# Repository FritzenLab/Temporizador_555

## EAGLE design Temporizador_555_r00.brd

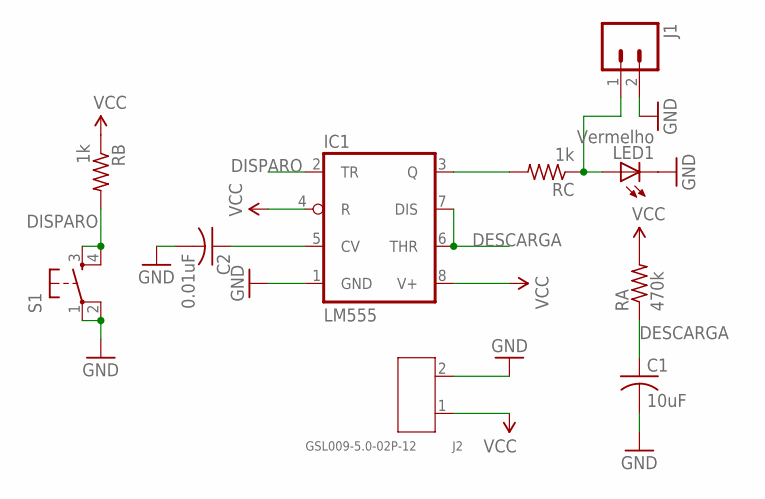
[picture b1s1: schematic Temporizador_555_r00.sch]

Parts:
C1: 10uF; C050-024X044
C2: 0.01uF; C050-024X044
IC1: LM555; DIL08-ROUND
J1: M02PTH; 1X02
J2: GSL009-5.0-02P-12; H2-5.0-10.5X8.0MM
LED1: Vermelho; LED5MM
RA: 470k; 0207/10
RB: 1k; 0207/10
RC: 1k; 0207/10
S1: TACTILE-SWITCH-PTH; TAC-SWITCH-PTH

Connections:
DESCARGA: C1.1, IC1.6 (THR), IC1.7 (DIS), RA.1
DISPARO: IC1.2 (TR), RB.2, S1.3, S1.4
GND: C1.2, C2.2, IC1.1 (GND), J1.2, J2.2, LED1.K (C), S1.1, S1.2
unnamed: C2.1, IC1.5 (CV)
unnamed: J1.1, LED1.A, RC.1
unnamed: IC1.3 (Q), RC.2
VCC: IC1.4 (R), IC1.8 (V+), J2.1, RA.2, RB.1

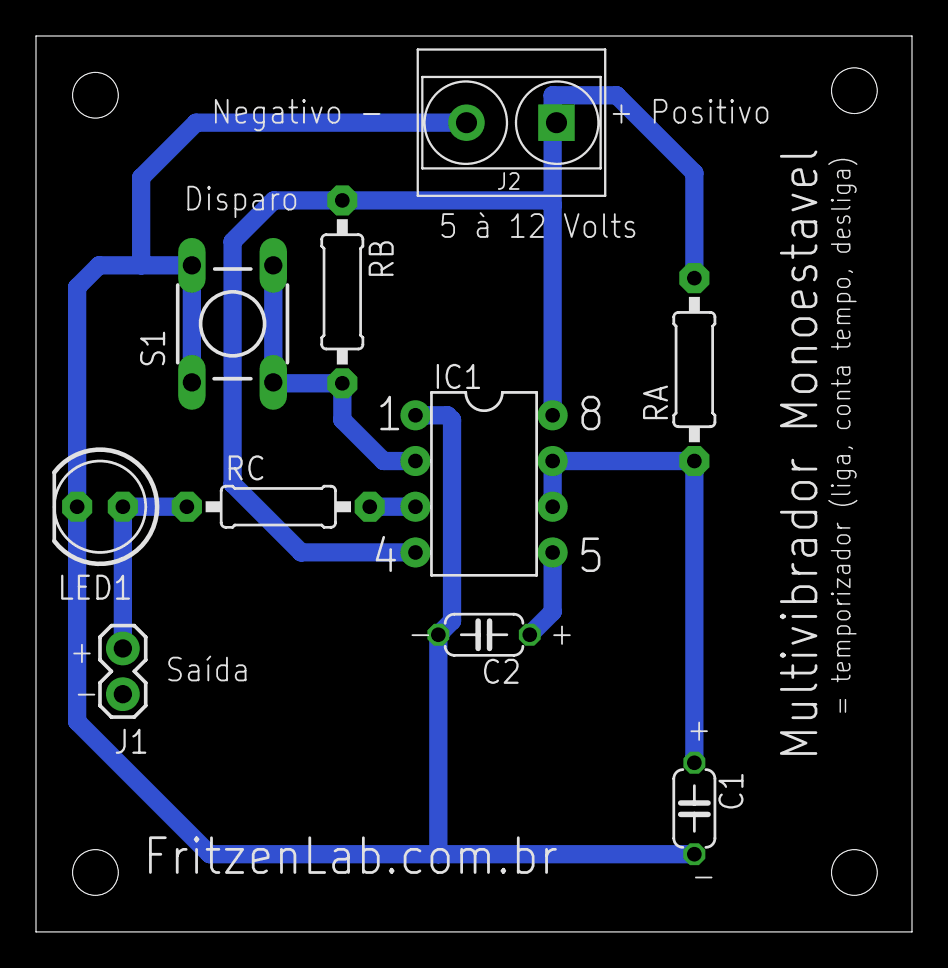
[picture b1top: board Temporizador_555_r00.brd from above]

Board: 2 copper layers, 48.7 x 49.8 mm, 10 parts (0 on the bottom side), 7 nets.

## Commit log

2016-03-02 Lançamento inicial de arquivos
    Upload inicial de diagrama esquematico e placa (layout) do temporizador
    educacional baseado no CI 555, em formato Eagle CAD
2016-04-01 Primeira revisao (r00) e arquivos para fabricacao
    Primeira revisao (estética e troca do conector da fonte por um KRE 5mm).
    Gerados Gerber para fabricaçao da PCI
2016-05-05 Upload de arquivos atuais que já foram para produção
    Upload de arquivos atuais que já foram produzidos
2016-05-05 Upload de arquivos atuais que foram para produção
    Upload de arquivos atuais que foram para produção
2019-02-10 revisao da PCI
    revisao da PCI
2024-11-03 generated gerbers r02
2024-11-03 added images

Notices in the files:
parts and their libraries:
GeekAmmo: Licensing:Creative Commons ShareAlike 4.0 International - https://creativecommons.org/licenses/by-sa/4.0
